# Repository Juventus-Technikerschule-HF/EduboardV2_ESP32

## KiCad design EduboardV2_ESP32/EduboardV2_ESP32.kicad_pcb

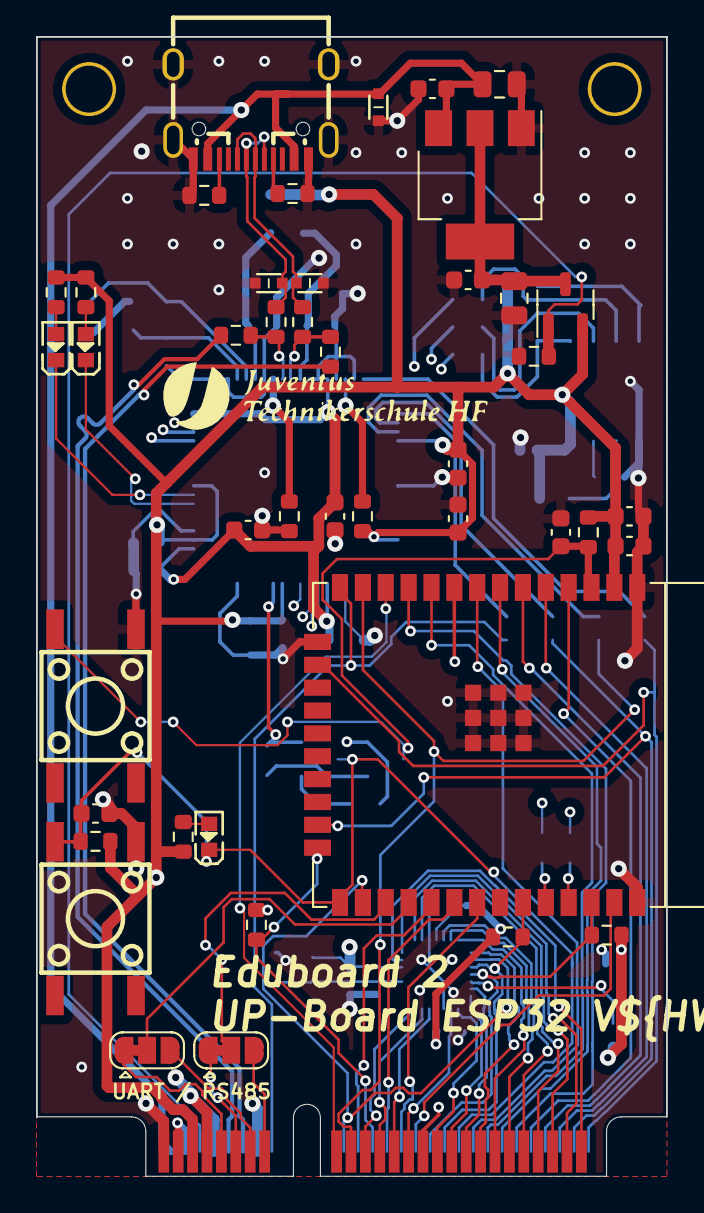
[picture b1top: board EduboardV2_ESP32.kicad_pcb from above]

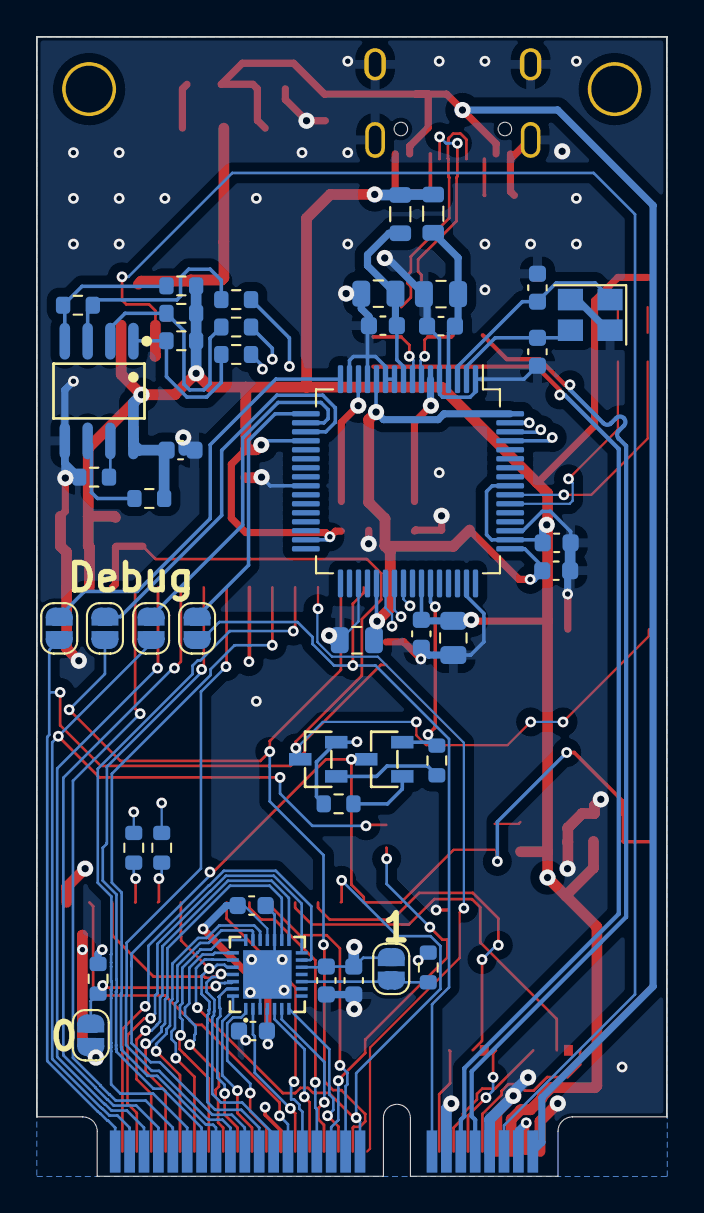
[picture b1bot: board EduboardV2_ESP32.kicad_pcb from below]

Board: 4 copper layers, 35.0 x 63.3 mm, 89 parts (45 on the bottom side), 93 nets.

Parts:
C1, C2: 12p; C_0603_1608Metric
C3, C8, C9, C10, C11, C12, C13, C14, C15, C16, C17, C18, C19, C22, C23, C24, C26, C28: 100n; C_0603_1608Metric
C4, C5, C6, C7, C25, C27: 4u7; C_0805_2012Metric
C20, C21: 1u; C_0603_1608Metric
D1, D2, D3: LESD5D5.0CT1G; SOD-523_L1.2-W0.8-LS1.6-BI
FB1, FB2: FerriteBead_Small; L_0805_2012Metric
J1: EduboardV2 PCIE UP Board Connector; mini-PCIe_F1_Full
JP1, JP2, JP3, JP4, JP5, JP6: SolderJumper_2_Open; SolderJumper-2_P1.3mm_Open_RoundedPad1.0x1.5mm
JP7, JP8: SolderJumper_3_Bridged12; SolderJumper-3_P1.3mm_Bridged12_RoundedPad1.0x1.5mm
LED1, LED2, LED3: 19-217/BHC-ZL1M2RY/3T; LED0603-FD_BLUE
Q1, Q2: S8050_C139514; SOT-23-3_L2.9-W1.3-P1.90-LS2.4-BR
Q3: AO3401A; SOT-23-3
R1, R13, R14, R22, R25: 2k2; R_0603_1608Metric
R2, R3, R4, R6, R7, R17, R18, R19, R20, R23, R24, R26, R27, R28: 10k; R_0603_1608Metric
R5, R15, R16, R21, R29, R30, R31, R32: 0R; R_0603_1608Metric
R8: 1k; R_0603_1608Metric
R9: 12k; R_0603_1608Metric
R10, R11, R12: 33R; R_0603_1608Metric
SW1, SW2: K2-1102SP-C4SC-04; KEY-SMD_4P-L6.0-W6.0-P4.50-LS9.5-BL
U1: ESP32-WROOM-E; ESP32-WROOM-32E
U2: FT2232HL; LQFP-64_10x10mm_P0.5mm
U3: M93C46-WMN6TP; SOIC-8_L4.9-W3.9-P1.27-LS6.0-BL
U4: SX1509BIULTRT; QFN-28_L4.0-W4.0-P0.40-BL-EP
U5: LD1117S33TR_SOT223; SOT-223-3_TabPin2
USBC1: USB3.1C16PFSMT; USB-C-SMD_TYPE-C-USB-17
Y2: 12MHz; Crystal_SMD_3225-4Pin_3.2x2.5mm

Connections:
3.3V_Sense: J1.6 (3.3V), Q3.1 (G), R25.1
+1V8: C4.2, C10.2, C11.2, C12.2, U2.12 (VCORE), U2.37 (VCORE), U2.49 (VREGOUT), U2.64 (VCORE)
+3V3: C3.1, C5.2, C13.2, C14.2, C15.2, C16.2, C19.1, C20.1, C21.2, C22.2, C23.1, C24.1, FB1.1, FB2.2, J1.5 (3.3V), JP5.2 (B), JP6.1 (A), Q3.2 (S), R2.1, R3.1, R4.1, R5.1, R8.1, R13.1, R14.1, R19.1, R20.1, R22.1, R27.1, R28.1, U1.2 (3V3), U2.20 (VCCIO), U2.31 (VCCIO), U2.42 (VCCIO), U2.50 (VREGIN), U2.56 (VCCIO), U3.8 (VCC), U4.4 (VCC1), U4.12 (VDDM), U4.18 (VCC2)
+5V: J1.3 (5V), J1.4 (5V)
/DebugChip FT2232HL/D_N: R29.2, R31.2, U2.7 (DM)
/DebugChip FT2232HL/D_P: R30.2, R32.2, U2.8 (DP)
D+: D2.2, R32.1, USBC1.A6 (DP1), USBC1.B6 (DP2)
D-: D3.2, R31.1, USBC1.A7 (DN1), USBC1.B7 (DN2)
EECLK: R2.2, R11.1, U3.2 (C)
EECS: R4.2, R10.1, U3.1 (S)
EEDATA: R1.2, R12.1, U3.3 (D)
ESP_EN: C17.1, Q1.3 (C), R19.2, SW2.2, U1.3 (EN/CHIP_PU)
ESP_IO0: C18.1, J1.34 (GPIOX4/AN5/I2S_MCLK), LED3.1 (C), Q2.3 (C), R20.2, SW1.2, U1.25 (GPIO0/BOOT/ADC2_CH1)
ESP_IO2: J1.22 (TFT_DC), R26.1, U1.24 (ADC2_CH2/GPIO2)
ESP_IO4: J1.18 (~General_Reset), U1.26 (ADC2_CH0/GPIO4), U4.23 (NRESET)
ESP_IO5: J1.20 (~TFT_CS), U1.29 (GPIO5)
ESP_IO16: JP8.2 (C), U1.27 (GPIO16)
ESP_IO17: JP7.2 (C), U1.28 (GPIO17)
ESP_IO18: J1.24 (SPI_SCK), U1.30 (GPIO18)
ESP_IO19: J1.26 (SPI_MISO), U1.31 (GPIO19)
ESP_IO21: J1.32 (SDA), R27.2, U1.33 (GPIO21), U4.24 (SDA)
ESP_IO22: J1.30 (SCL), R28.2, U1.36 (GPIO22), U4.25 (SCL)
ESP_IO23: J1.28 (SPI_MOSI), U1.37 (GPIO23)
ESP_IO25: J1.38 (GPIOX2/AN3/I2S_LRCK), U1.10 (DAC_1/ADC2_CH8/GPIO25)
ESP_IO26: J1.42 (GPIOX0/AN1/I2S_DOUT), U1.11 (DAC_2/ADC2_CH9/GPIO26)
ESP_IO27: J1.17 (~FLASH_CS), U1.12 (ADC2_CH7/GPIO27)
ESP_IO32: J1.36 (GPIOX3/AN4/I2S_SCLK), U1.8 (32K_XP/GPIO32/ADC1_CH4)
ESP_IO33: J1.29 (WS2812_Data), U1.9 (32K_XN/GPIO33/ADC1_CH5)
ESP_IO34: J1.46 (SW0), U1.6 (GPIO34/ADC1_CH6)
ESP_IO35: J1.40 (GPIOX1/AN2/I2S_DIN), U1.7 (GPIO35/ADC1_CH7)
ESP_IO36: J1.44 (AN0/Pot0), U1.4 (SENSOR_VP/GPIO36/ADC1_CH0)
ESP_IO39: J1.48 (SW1), U1.5 (SENSOR_VN/GPIO39/ADC1_CH3)
ESP_RXD: R16.1, U1.34 (U0RXD/GPIO3)
ESP_TCK: J1.52 (SW3), JP1.2 (B), U1.16 (MTCK/GPIO13/ADC2_CH4)
ESP_TDI: J1.16 (RS485_DE), JP2.2 (B), U1.14 (MTDI/GPIO12/ADC2_CH5)
ESP_TDO: J1.50 (SW2), JP3.2 (B), U1.23 (MTDO/GPIO15/ADC2_CH3)
ESP_TMS: J1.19 (~SD_CS), JP4.2 (B), U1.13 (MTMS/GPIO14/ADC2_CH6)
ESP_TXD: R15.1, U1.35 (U0TXD/GPIO1)
FT_RXD: R15.2, U2.39 (BDBUS1)
FT_TCK: JP1.1 (A), U2.16 (ADBUS0)
FT_TDI: JP2.1 (A), U2.17 (ADBUS1)
FT_TDO: JP3.1 (A), U2.18 (ADBUS2)
FT_TMS: JP4.1 (A), U2.19 (ADBUS3)
FT_TXD: R16.2, U2.38 (BDBUS0)
FT_nDTR: Q2.2 (E), R17.1, U2.43 (BDBUS4)
FT_nRTS: Q1.2 (E), R18.1, U2.40 (BDBUS2)
GND: C1.2, C2.2, C3.2, C4.1, C5.1, C6.1, C7.1, C8.1, C9.1, C10.1, C11.1, C12.1, C13.1, C14.1, C15.1, C16.1, C17.2, C18.2, C19.2, C20.2, C21.1, C22.1, C23.2, C24.2, C25.1, C26.1, C27.1, C28.1, D1.1, D2.1, D3.1, J1.1 (GND), J1.7 (GND), J1.8 (GND), J1.14 (GND), R6.2, R7.2, R9.1, R21.2, R23.1, R24.2, R25.2, R26.2, SW1.4, SW2.4, U1.1 (GND), U1.15 (GND), U1.38 (GND), U1.39 (GND_THERMAL), U2.1 (GND), U2.5 (GND), U2.10 (AGND), U2.11 (GND), U2.13 (TEST), U2.15 (GND), U2.25 (GND), U2.35 (GND), U2.47 (GND), U2.51 (GND), U3.5 (VSS), U4.0 (PAD), U4.3 (GND), U4.17 (GND), U5.1 (GND), USBC1.0, USBC1.A1 (GND), USBC1.A12 (GND), Y2.2, Y2.4
GPIO_Buzzer: J1.27 (Buzzer), U4.2 (I/O[3])
GPIO_LED0: J1.37 (LED0), U4.22 (I/O[15])
GPIO_LED1: J1.39 (LED1), U4.21 (I/O[14])
GPIO_LED2: J1.41 (LED2), U4.20 (I/O[13])
GPIO_LED3: J1.43 (LED3), U4.19 (I/O[12])
GPIO_LED4: J1.45 (LED4), U4.16 (I/O[11])
GPIO_LED5: J1.47 (LED5), U4.15 (I/O[10])
GPIO_LED6: J1.49 (LED6), U4.14 (I/O[9])
GPIO_LED7: J1.51 (LED7), U4.13 (I/O[8])
GPIO_PWM_B: J1.35 (PWM_B), U4.27 (I/O[0])
GPIO_PWM_G: J1.33 (PWM_G), U4.28 (I/O[1])
GPIO_PWM_R: J1.31 (PWM_R), U4.1 (I/O[2])
GPIO_RotEnc_A: J1.23 (RotEnc_A), U4.6 (I/O[5])
GPIO_RotEnc_B: J1.21 (RotEnc_B), U4.7 (I/O[6])
GPIO_RotEnc_SW: J1.25 (RotEnc_SW), U4.5 (I/O[4])
unnamed: J1.11 (UART0_UP_RX), JP8.1 (A)
unnamed: J1.9 (UART0_UP_TX), JP7.1 (A)
unnamed: J1.15 (UART1_RS485_RX), JP8.3 (B)
unnamed: J1.13 (UART1_RS485_TX), JP7.3 (B)
unnamed: JP5.1 (A), R23.2, U4.26 (ADDR0)
unnamed: JP6.2 (B), R24.1, U4.10 (ADDR1)
unnamed: LED1.2 (A), R13.2
unnamed: LED1.1 (C), U2.54 (BCBUS3)
unnamed: LED2.2 (A), R14.2
unnamed: LED2.1 (C), U2.55 (BCBUS4)
unnamed: LED3.2 (A), R22.2
unnamed: Q1.1 (B), R17.2
unnamed: Q2.1 (B), R18.2
unnamed: C27.2, C28.2, Q3.3 (D), U5.2 (VO)
unnamed: R11.2, U2.62 (EECLK)
unnamed: R10.2, U2.63 (EECS)
unnamed: R12.2, U2.61 (EEDATA)
unnamed: C2.1, U2.2 (OSCI), Y2.3
unnamed: C1.1, U2.3 (OSCO), Y2.1
unnamed: R9.2, U2.6 (REF)
unnamed: C6.2, C9.2, FB2.1, U2.4 (VPHY)
unnamed: C7.2, C8.2, FB1.2, U2.9 (VPLL)
unnamed: R8.2, U2.14 (~RESET)
unnamed: R21.1, U3.7 (DU)
unnamed: R5.2, U3.6 (ORG)
unnamed: R1.1, R3.2, U3.4 (Q)
unnamed: R7.1, USBC1.A5 (CC1)
unnamed: R6.1, USBC1.B5 (CC2)
USB_Debug_D+: J1.12 (USB_Debug_D+), R30.1
USB_Debug_D-: J1.10 (USB_Debug_D-), R29.1
VBUS: C25.2, C26.2, D1.2, J1.2 (V_USB), U5.3 (VI), USBC1.A4 (VBUS), USBC1.A9 (VBUS)

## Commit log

2023-03-15 work on debug chip
2023-03-16 finalize ft2232 design, prepare esp pins, work on mpcie pinout
2023-03-20 add Portexpander, connect mPCIE
2023-03-20 all parts placed. descision about usb-debug line to be made...
2023-03-20 add voltage selector to prevent fighting sources
2023-03-21 rework pin assignement with esp32 pin restrictions in mind. start layout
2023-03-21 resize mPCIE Board Footprint, work on ESP32 UP Board
2023-03-23 work on layout
2023-04-08 layout done so far. Have to check everything and work on footprints in general. Changed to 4 layer (was not possible otherwise)
2023-04-11 finalize Layout, fill in most of the critical part info. Replace certain parts with Eduboard kicadlib Parts.
2023-04-12 finalize Data. Add Logo and Text
2023-04-12 add gnd vias. Improve USB Diff Line. Work on finalization of pcb
2023-04-16 add schematic V1 as PDF
2023-04-25 update 3d render of pcb for baseboard 3d render
